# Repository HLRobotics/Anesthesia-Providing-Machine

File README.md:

# Anesthesia-Providing-Machine
 Fuzzy Logic based Anasthesia Dispensor

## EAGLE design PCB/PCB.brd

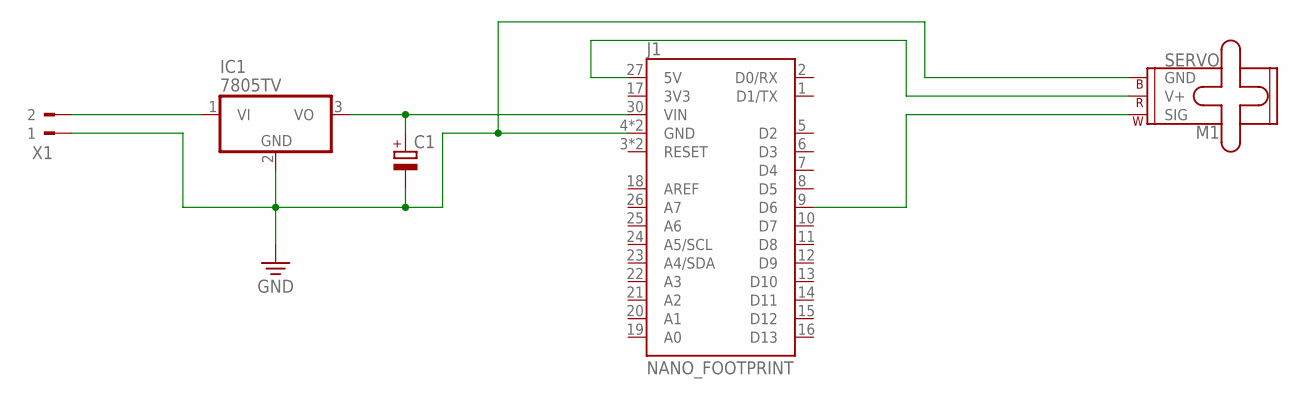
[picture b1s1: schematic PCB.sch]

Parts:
C1: C-POL_RADIAL-32MM-DIA; CAPPRD1000W100D2275H3200B
IC1: 7805TV; TO220V
J1: NANO_FOOTPRINT; NANO
M1: SERVO; 1X03
X1: 90-2

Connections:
GND: C1.2 (-), IC1.2 (GND), J1.4 (GND), J1.29 (GND), M1.3 (GND), X1.1
unnamed: IC1.1 (VI), X1.2
unnamed: C1.1 (+), IC1.3 (VO), J1.30 (VIN)
unnamed: J1.9 (D6), M1.1 (SIG)
unnamed: J1.27 (5V), M1.2 (V+)

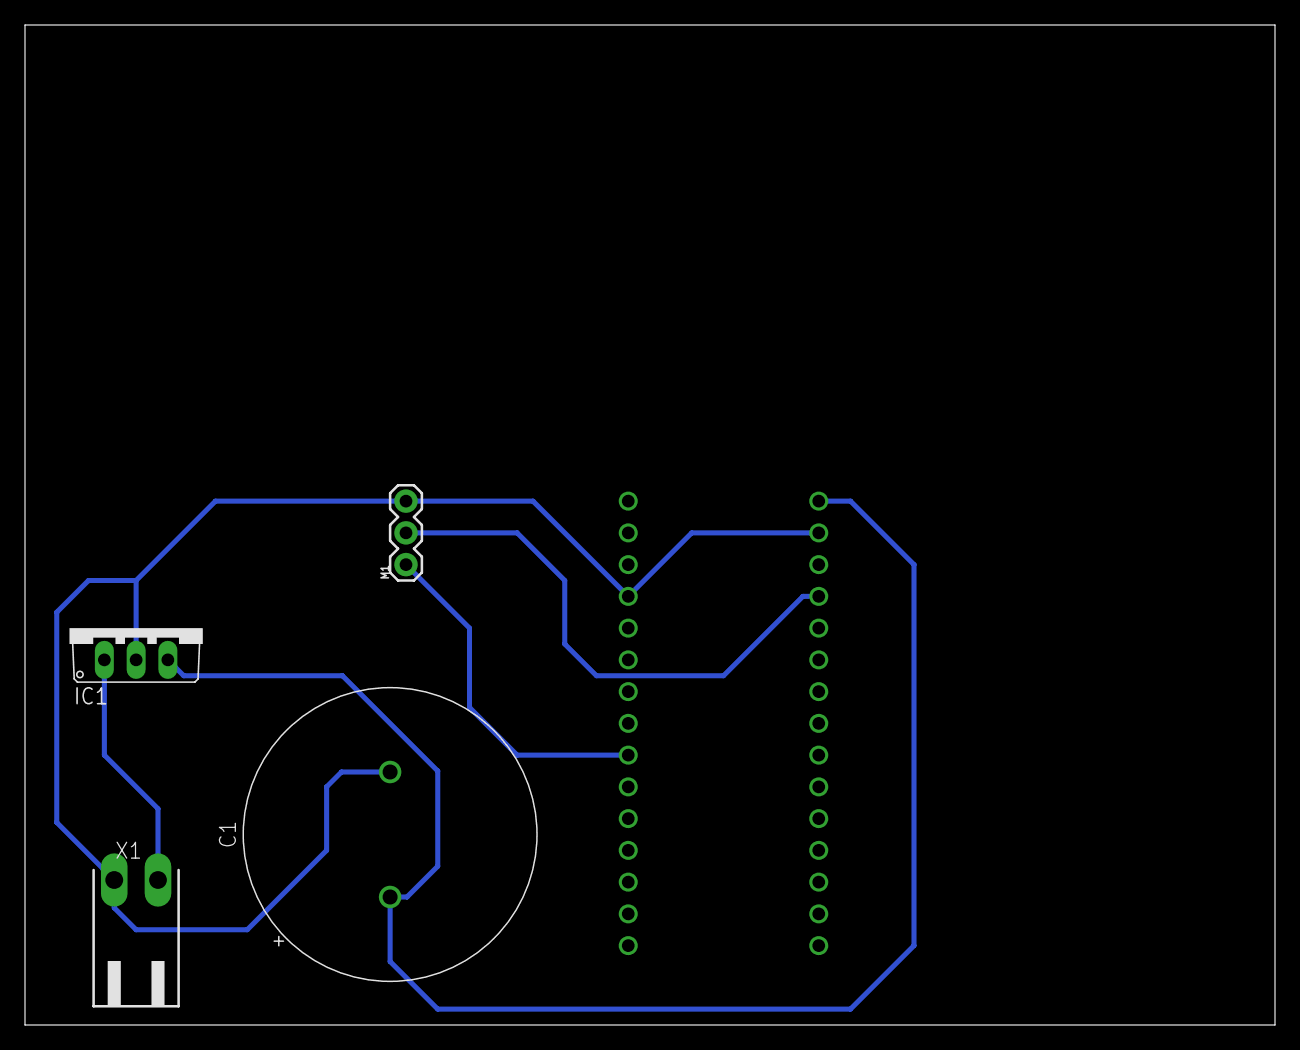
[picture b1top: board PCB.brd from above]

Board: 2 copper layers, 100.0 x 80.0 mm, 5 parts (0 on the bottom side), 5 nets.

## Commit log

2021-06-03 licence
2021-06-10 Final Updates
2021-06-13 methodology
2021-07-16 minor fix

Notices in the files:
parts and their libraries:
SparkFun-Boards: Licensing: Creative Commons ShareAlike 4.0 International - https://creativecommons.org/licenses/by-sa/4.0
